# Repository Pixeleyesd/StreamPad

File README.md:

# StreamPad
The StreamPad is an open source hackpad made for macros (designed for streaming). It has 16 keys (4x4) and an OLED screen.

# PCB
Designed with KiCad.

# Case
Designed with fusion 360.

The macropad is assembled by pressing heat-set inserts into the back of the top plate. Then, 16mm screws are inserted through the bottom of the base and the PCB, threading directly into the inserts to hold everything together.

# Firmware
The firmware is written in KMK.

You will need to flash the .uf2 provided in the Firmware folder in this repo to the Seeeduino XIAO. (Refer to help here: https://wiki.seeedstudio.com/XIAO-RP2040-with-CircuitPython/)

After this, drag the files in the circuitpy folder provided in this repo into the CIRCUITPY drive that shows up after flashing circuitpython to the microcontroller. Do this as you would a flash drive.

# Assemble
Bill Of Materials (BOM):

1x XIAO RP2040

16x Cherry MX Switches

16x DSA Keycaps

4x M3x5x4 Heatset inserts

4x M3x16mm screws

16x 1N4148 DO-35 Diodes

1x 0.91" 128x32 OLED Display

My 3D printed case (Top & Bottom)

My PCB design. (I'm planning to use JLCPCB for the custom assembly of it)

You will also need to solder wires from XIAO to OLED. The wires will be self-provided: 

GND -> GND

3v3 -> VCC

D4 -> SDA

D5 -> SCL

You will then need to attach the OLED onto the top half of the case.

---

This was my first time ever using KiCad for PCB design, and my first time properly shipping an open source project like this. I learned a lot about this sort of stuff with this project, and made many mistakes I will remember not to make again lol.
Thanks to the Hackclub (and Stardance) team for providing these amazing resources that helped make this dream of mine come true :3

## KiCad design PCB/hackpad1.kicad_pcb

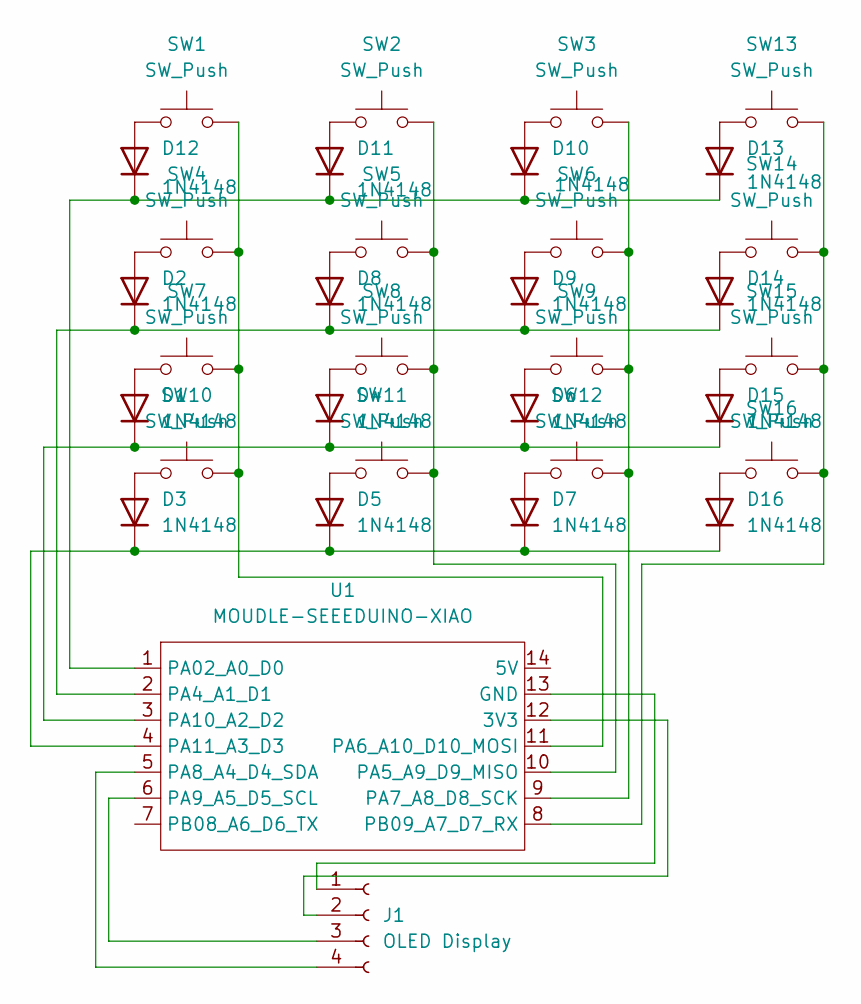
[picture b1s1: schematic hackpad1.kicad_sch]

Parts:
D1, D2, D3, D4, D5, D6, D7, D8, D9, D10, D11, D12, D13, D14, D15, D16: 1N4148; D_DO-35_SOD27_P7.62mm_Horizontal
J1: OLED Display
SW1, SW2, SW3, SW4, SW5, SW6, SW7, SW8, SW9, SW10, SW11, SW12, SW13, SW14, SW15, SW16: SW_Push; SW_Cherry_MX_1.00u_PCB
U1: MOUDLE-SEEEDUINO-XIAO; XIAO-Generic-Hybrid-14P-2.54-21X17.8MM

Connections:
unnamed: D1.2 (A), SW7.1
unnamed: D1.1 (K), D4.1 (K), D6.1 (K), D15.1 (K), U1.3 (PA10_A2_D2)
unnamed: D2.2 (A), SW4.1
unnamed: D3.2 (A), SW10.1
unnamed: D4.2 (A), SW8.1
unnamed: D5.2 (A), SW11.1
unnamed: D6.2 (A), SW9.1
unnamed: D7.2 (A), SW12.1
unnamed: D8.2 (A), SW5.1
unnamed: D9.2 (A), SW6.1
unnamed: D10.2 (A), SW3.1
unnamed: D10.1 (K), D11.1 (K), D12.1 (K), D13.1 (K), U1.1 (PA02_A0_D0)
unnamed: D11.2 (A), SW2.1
unnamed: D12.2 (A), SW1.1
unnamed: D13.2 (A), SW13.1
unnamed: D14.2 (A), SW14.1
unnamed: D2.1 (K), D8.1 (K), D9.1 (K), D14.1 (K), U1.2 (PA4_A1_D1)
unnamed: D15.2 (A), SW15.1
unnamed: D16.2 (A), SW16.1
unnamed: D3.1 (K), D5.1 (K), D7.1 (K), D16.1 (K), U1.4 (PA11_A3_D3)
unnamed: J1.1, U1.13 (GND)
unnamed: J1.2, U1.12 (3V3)
unnamed: J1.3, U1.6 (PA9_A5_D5_SCL)
unnamed: J1.4, U1.5 (PA8_A4_D4_SDA)
unnamed: SW2.2, SW5.2, SW8.2, SW11.2, U1.10 (PA5_A9_D9_MISO)
unnamed: SW1.2, SW4.2, SW7.2, SW10.2, U1.11 (PA6_A10_D10_MOSI)
unnamed: SW3.2, SW6.2, SW9.2, SW12.2, U1.9 (PA7_A8_D8_SCK)
unnamed: SW13.2, SW14.2, SW15.2, SW16.2, U1.8 (PB09_A7_D7_RX)

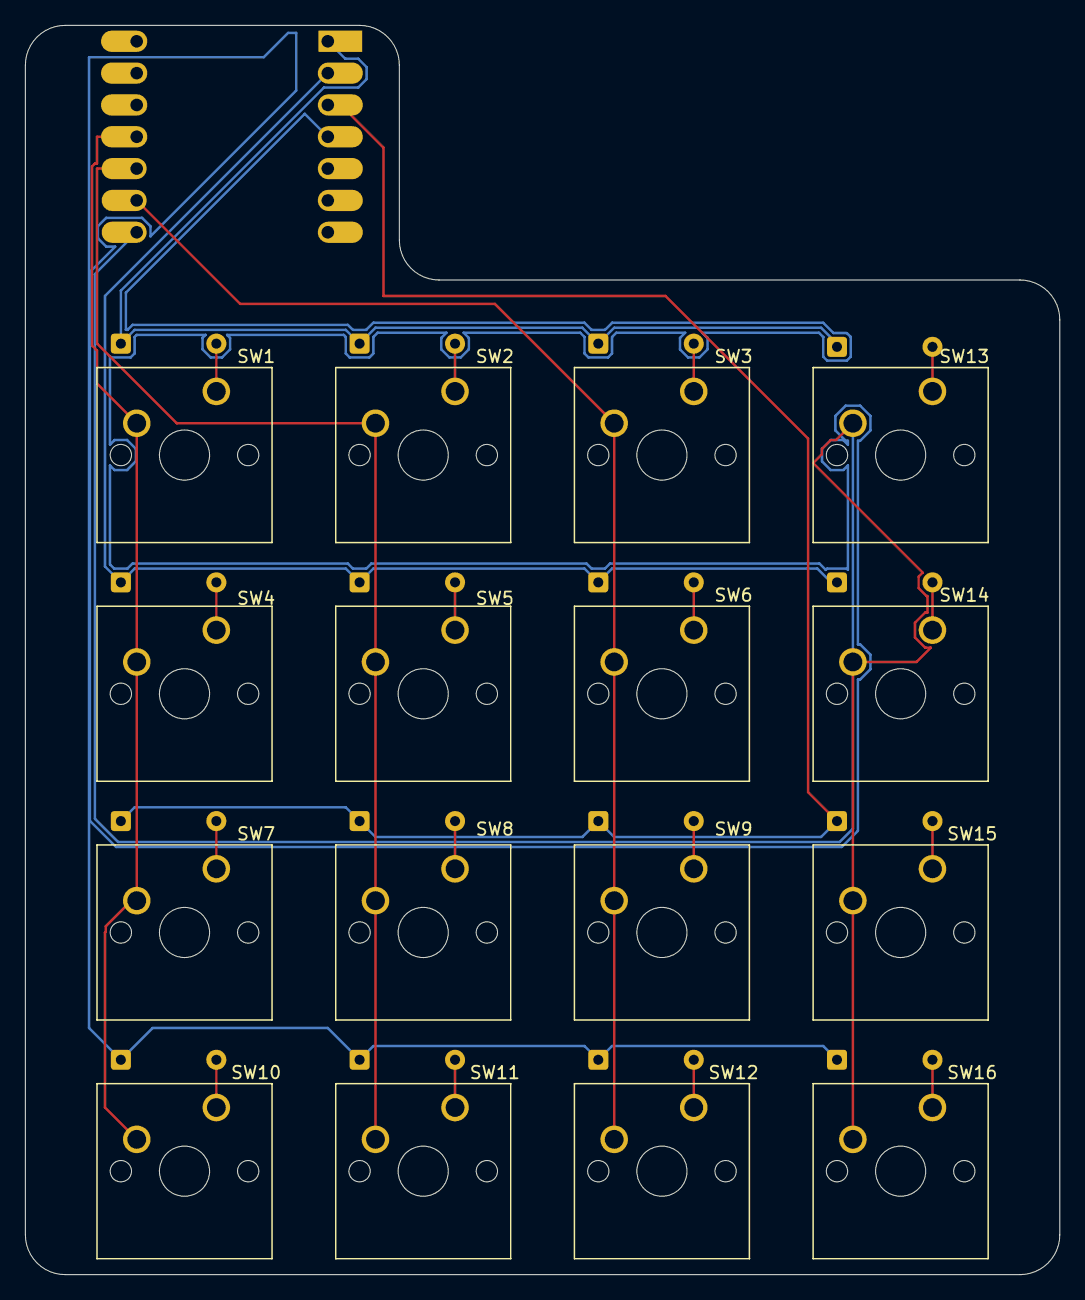
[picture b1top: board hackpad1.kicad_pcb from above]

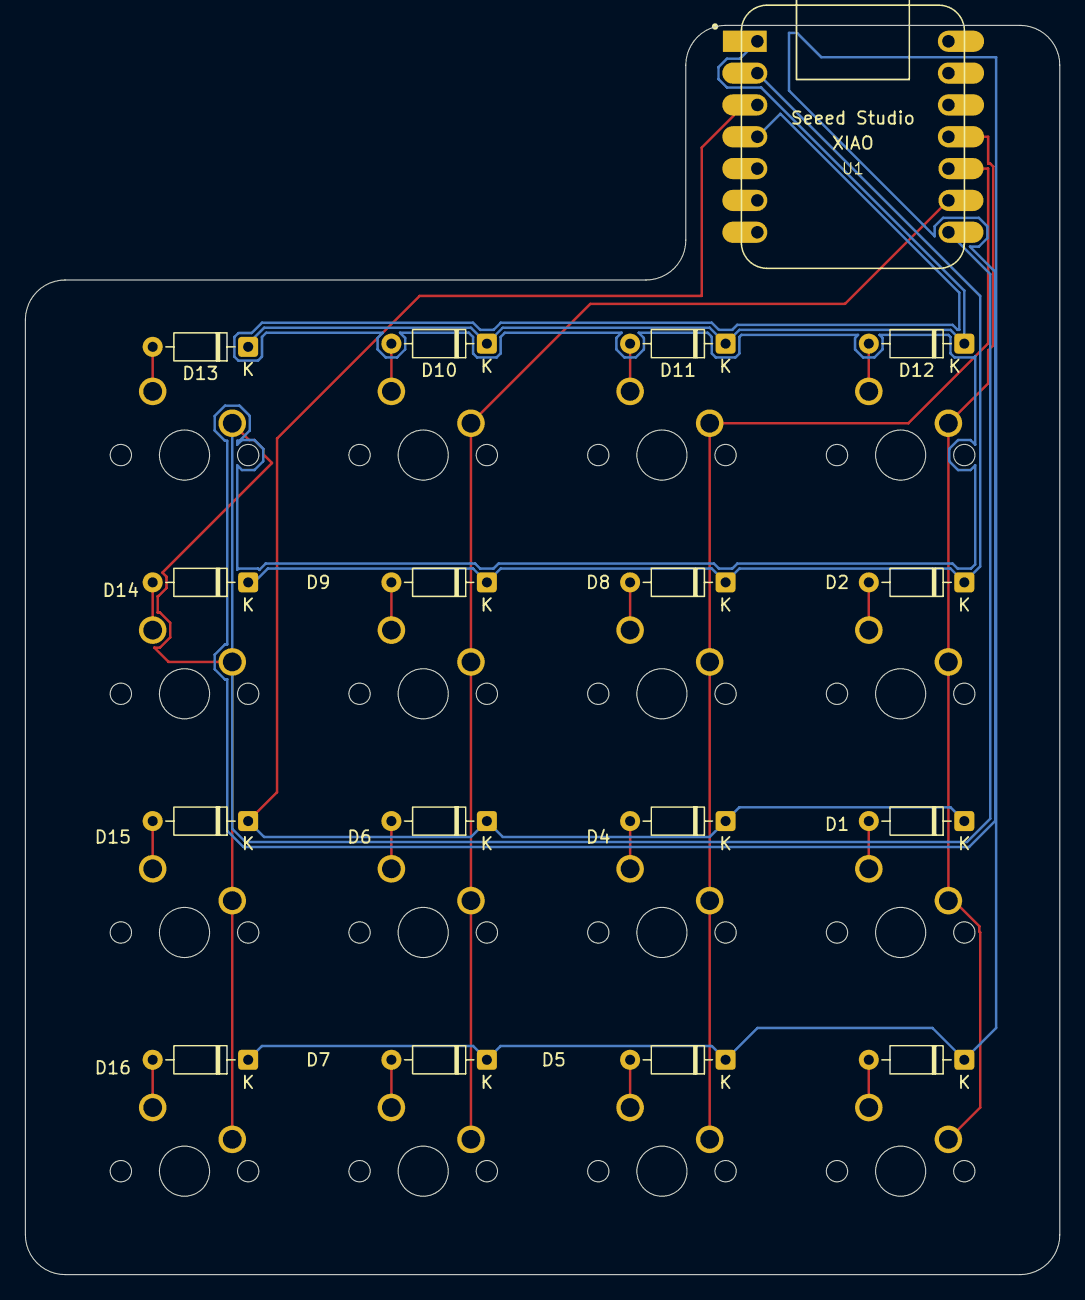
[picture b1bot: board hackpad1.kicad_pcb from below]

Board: 2 copper layers, 82.5 x 99.7 mm, 33 parts (17 on the bottom side), 24 nets.

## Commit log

2026-06-22 Fix styling errors in README.md
2026-06-22 Update PCB gluing recommendation in README
    Clarified recommendation for gluing PCB in case.
2026-06-22 Rename 'Build' section to 'Assemble'
2026-06-22 Added StreamPad case files
    Provided in .STEP format to preserve exact geometry.
2026-06-22 Revise PCB design assembly recommendation
    Updated the recommendation for PCB design assembly process.
2026-06-22 Added the gerbers.zip for the PCB
2026-06-22 Update README with firmware and flashing instructions
    Added firmware details and flashing instructions for Seeeduino XIAO.
2026-06-22 move StreamPadBottom.step into folder "Print Files"
2026-06-22 move StreamPadTop.step into folder "Print Files"
2026-06-22 move gerbers.zip to folder PCB
2026-06-22 firmware :)
2026-06-22 move .uf2 file into folder Firmware
2026-06-22 Clarify .uf2 file location in README
    Updated README to specify the Firmware folder for .uf2 file.
2026-06-22 cool kmk stuff
2026-06-22 Create directory circuitpy
2026-06-22 add kmk, this time in the circuitpy folder
2026-06-22 added libraries
2026-06-22 Rename circuitpy/adafruit_displayio_ssd1306.mpy to circuitpy/lib/adafruit_displayio_ssd1306.mpy
2026-06-22 added adafruit display text folder
    added adafruit display text in libs folder this time
2026-06-22 Clarify wiring instructions for XIAO to OLED
2026-06-22 Add note regarding repo restructuring for submission
    Added a note about restructuring the repository for submission.
2026-06-22 Restructured the whole repo for stardance submission
2026-06-22 Fix heights
2026-06-22 Add images of completed design
2026-06-22 Rename Screenshot 2026-06-22 204807.png to completedesign1
2026-06-22 Rename Screenshot 2026-06-22 204755.png to completedesign2
2026-06-22 Add pictures to README.md
2026-06-22 Fix Pictures
2026-06-22 Rename completedesign2 to completedesign2.png
2026-06-22 Rename completedesign1 to completedesign1.png
2026-06-22 add full case CAD file
    add full case CAD file (.STEP file format)
2026-06-22 Remove restructuring note from README
    Removed note about repo restructuring.
2026-06-22 Revise components list and add assembly notes
    Updated the components list and added notes about the 3D printed case and PCB design.
2026-06-22 updated PCB design to fit requirements for stardance
2026-06-22 Added additional PCB image
